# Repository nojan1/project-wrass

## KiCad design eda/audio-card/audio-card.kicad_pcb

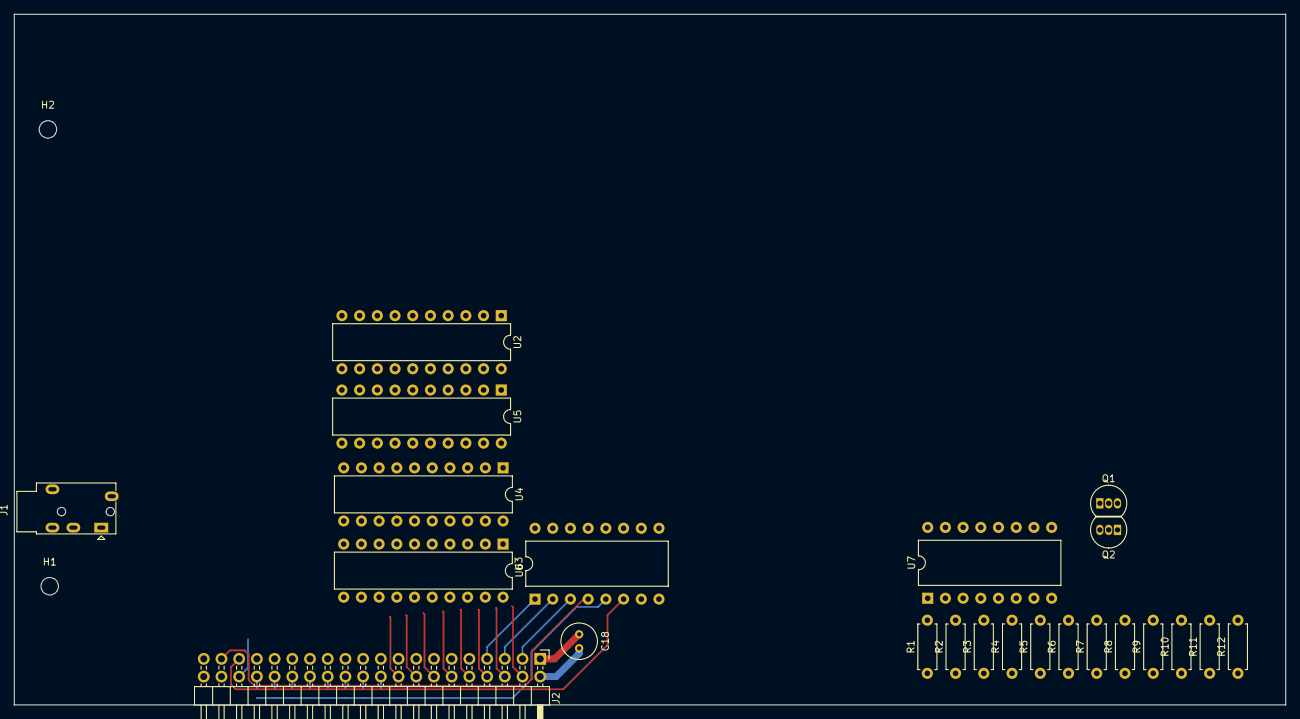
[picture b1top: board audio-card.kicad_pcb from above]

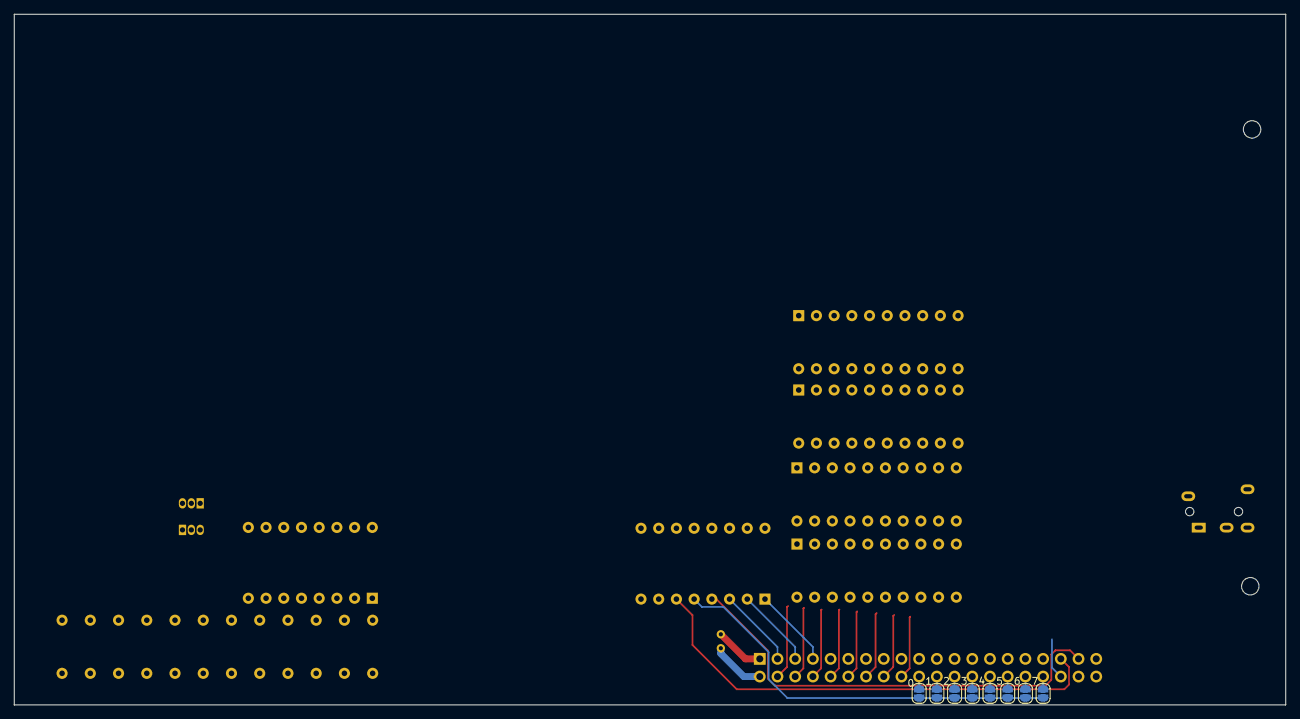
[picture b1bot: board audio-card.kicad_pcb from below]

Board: 2 copper layers, 182.4 x 99.1 mm, 33 parts (8 on the bottom side), 39 nets.

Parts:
C18: 100nf; C_Radial_D5.0mm_H7.0mm_P2.00mm
H1, H2: Bracket mounting; MountingHole_2.5mm
J1: AudioJack2_SwitchT; Jack_3.5mm_PJ320E_Horizontal
J2: Bus expansion; PinHeader_2x20_P2.54mm_Horizontal
JP1, JP2, JP3, JP4, JP5, JP6, JP7, JP8: SolderJumper_2_Open; SolderJumper-2_P1.3mm_Open_RoundedPad1.0x1.5mm
Q1, Q2: BC558; TO-92_Inline
R1, R2, R3: 100k; R_Axial_DIN0207_L6.3mm_D2.5mm_P7.62mm_Horizontal
R4: 100R; R_Axial_DIN0207_L6.3mm_D2.5mm_P7.62mm_Horizontal
R5: 200k; R_Axial_DIN0207_L6.3mm_D2.5mm_P7.62mm_Horizontal
R6: 33k; R_Axial_DIN0207_L6.3mm_D2.5mm_P7.62mm_Horizontal
R7, R8, R9: 10k; R_Axial_DIN0207_L6.3mm_D2.5mm_P7.62mm_Horizontal
R10, R11: 470k; R_Axial_DIN0207_L6.3mm_D2.5mm_P7.62mm_Horizontal
R12: 1k; R_Axial_DIN0207_L6.3mm_D2.5mm_P7.62mm_Horizontal
U2, U4, U5, U6: 74HCT574; DIP-20_W7.62mm
U3: 74HCT138; DIP-16_W10.16mm
U7: TL074; DIP-16_W10.16mm

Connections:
+12V: R1.1, R2.1
/Channel/D0: J2.4, U2.2 (D0), U4.2 (D0), U5.2 (D0), U6.2 (D0)
/Channel/D1: J2.6, U2.3 (D1), U4.3 (D1), U5.3 (D1), U6.3 (D1)
/Channel/D2: J2.8, U2.4 (D2), U4.4 (D2), U5.4 (D2), U6.4 (D2)
/Channel/D3: J2.10, U2.5 (D3), U4.5 (D3), U5.5 (D3), U6.5 (D3)
/Channel/D4: J2.12, U2.6 (D4), U4.6 (D4), U5.6 (D4), U6.6 (D4)
/Channel/D5: J2.14, U2.7 (D5), U4.7 (D5), U5.7 (D5), U6.7 (D5)
/Channel/D6: J2.16, U2.8 (D6), U4.8 (D6), U5.8 (D6), U6.8 (D6)
/Channel/D7: J2.18, U2.9 (D7), U4.9 (D7), U5.9 (D7), U6.9 (D7)
/Channel/~NoteLatch: U2.11 (Cp), U3.14 (O1)
/Channel/~OctaveLatch: U3.15 (O0), U6.11 (Cp)
/Channel/~VolumeLatch: U3.13 (O2), U4.11 (Cp)
/Expansion/A0: J2.3, U3.3 (A2)
/Expansion/A1: J2.5, U3.2 (A1)
/Expansion/A2: J2.7, U3.1 (A0)
/Expansion/Clock: J2.35, U3.6 (E3)
/Expansion/GND: C18.2, J2.2
/Expansion/R~W: J2.37, U3.4 (E1)
/Expansion/VCC: C18.1, J2.1
/Expansion/~CS: JP1.2 (B), JP2.2 (B), JP3.2 (B), JP4.2 (B), JP5.2 (B), JP6.2 (B), JP7.2 (B), JP8.2 (B), U3.5 (E2)
GND: Q2.2 (B), R4.2, R10.2, U2.1 (OE), U2.10 (GND), U4.1 (OE), U4.10 (GND), U5.1 (OE), U5.10 (GND), U6.1 (OE), U6.10 (GND), U7.3 (+)
unnamed: J2.20, JP1.1 (A)
unnamed: J2.22, JP2.1 (A)
unnamed: J2.24, JP3.1 (A)
unnamed: J2.26, JP4.1 (A)
unnamed: J2.28, JP5.1 (A)
unnamed: J2.30, JP6.1 (A)
unnamed: J2.32, JP7.1 (A)
unnamed: J2.34, JP8.1 (A)
unnamed: Q1.2 (B), R3.2, R4.1
unnamed: Q1.1 (C), R1.2, R7.1
unnamed: Q1.3 (E), Q2.3 (E), R9.1
unnamed: Q2.1 (C), R2.2, R8.1
unnamed: R6.2, R9.2, U7.1
unnamed: R11.2, R12.1, U7.7
unnamed: R5.1, R6.1, U7.2 (-)
unnamed: R8.2, R10.1, U7.5 (+)
unnamed: R7.2, R11.1, U7.6 (-)
VCC: U2.20 (VCC), U4.20 (VCC), U5.20 (VCC), U6.20 (VCC)

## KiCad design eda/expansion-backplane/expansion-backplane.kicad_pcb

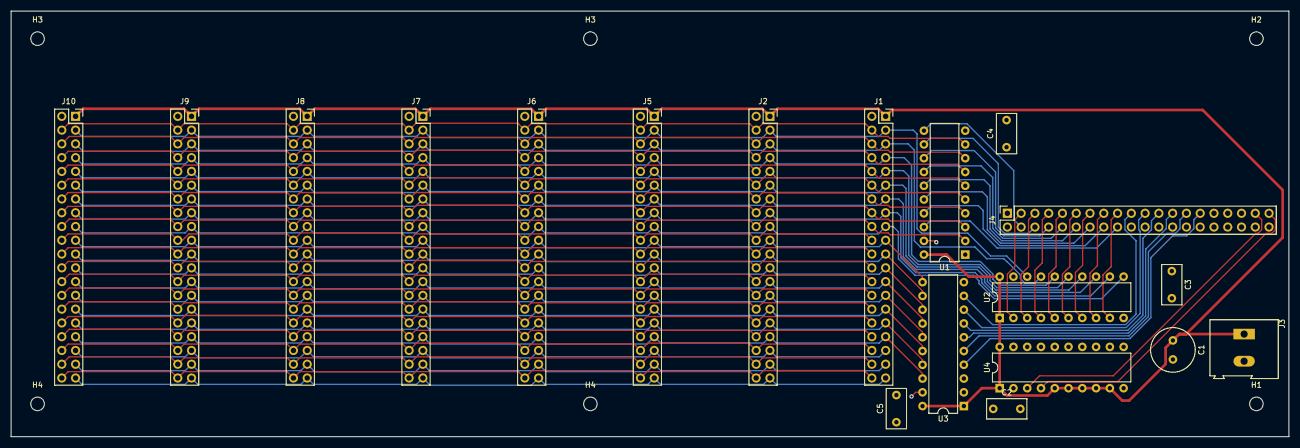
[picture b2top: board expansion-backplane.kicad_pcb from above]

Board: 2 copper layers, 235.7 x 78.5 mm, 25 parts (0 on the bottom side), 67 nets.

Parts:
C1: 1u; C_Radial_D8.0mm_H7.0mm_P3.50mm
C2, C3, C4, C5: 100nf; C_Rect_L7.2mm_W3.5mm_P5.00mm_FKS2_FKP2_MKS2_MKP2
H1, H2, H3, H3#2, H4, H4#2: MountingHole; MountingHole_2.5mm
J1: OUT1; PinSocket_2x20_P2.54mm_Vertical
J2: OUT5; PinSocket_2x20_P2.54mm_Vertical
J3: PWR; TerminalBlock_Altech_AK300-2_P5.00mm
J4: IN; PinSocket_2x20_P2.54mm_Vertical
J5: OUT2; PinSocket_2x20_P2.54mm_Vertical
J6: OUT6; PinSocket_2x20_P2.54mm_Vertical
J7: OUT3; PinSocket_2x20_P2.54mm_Vertical
J8: OUT7; PinSocket_2x20_P2.54mm_Vertical
J9: OUT4; PinSocket_2x20_P2.54mm_Vertical
J10: OUT8; PinSocket_2x20_P2.54mm_Vertical
U1, U2, U3, U4: 74HCT245; DIP-20_W7.62mm

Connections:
/IA0: J4.3, U2.2 (A0)
/IA1: J4.5, U2.3 (A1)
/IA2: J4.7, U2.4 (A2)
/IA3: J4.9, U2.5 (A3)
/IA4: J4.11, U2.6 (A4)
/IA5: J4.13, U2.7 (A5)
/IA6: J4.15, U2.8 (A6)
/IA7: J4.17, U2.9 (A7)
/IA8: J4.19, U3.9 (A7)
/IA9: J4.21, U3.8 (A6)
/IA10: J4.23, U3.7 (A5)
/IA11: J4.25, U3.6 (A4)
/IA12: J4.27, U3.5 (A3)
/IA13: J4.29, U3.4 (A2)
/IA14: J4.31, U3.3 (A1)
/IA15: J4.33, U3.2 (A0)
/IClock: J4.35, U4.2 (A0)
/ID0: J4.4, U1.11 (B7)
/ID1: J4.6, U1.12 (B6)
/ID2: J4.8, U1.13 (B5)
/ID3: J4.10, U1.14 (B4)
/ID4: J4.12, U1.15 (B3)
/ID5: J4.14, U1.16 (B2)
/ID6: J4.16, U1.17 (B1)
/ID7: J4.18, U1.18 (B0)
/IR~W: J4.37, U1.1 (A->B), U4.3 (A1)
/I~DMA: J4.39, U4.4 (A2)
A0: J1.3, J2.3, J5.3, J6.3, J7.3, J8.3, J9.3, J10.3, U2.18 (B0)
A1: J1.5, J2.5, J5.5, J6.5, J7.5, J8.5, J9.5, J10.5, U2.17 (B1)
A2: J1.7, J2.7, J5.7, J6.7, J7.7, J8.7, J9.7, J10.7, U2.16 (B2)
A3: J1.9, J2.9, J5.9, J6.9, J7.9, J8.9, J9.9, J10.9, U2.15 (B3)
A4: J1.11, J2.11, J5.11, J6.11, J7.11, J8.11, J9.11, J10.11, U2.14 (B4)
A5: J1.13, J2.13, J5.13, J6.13, J7.13, J8.13, J9.13, J10.13, U2.13 (B5)
A6: J1.15, J2.15, J5.15, J6.15, J7.15, J8.15, J9.15, J10.15, U2.12 (B6)
A7: J1.17, J2.17, J5.17, J6.17, J7.17, J8.17, J9.17, J10.17, U2.11 (B7)
A8: J1.19, J2.19, J5.19, J6.19, J7.19, J8.19, J9.19, J10.19, U3.11 (B7)
A9: J1.21, J2.21, J5.21, J6.21, J7.21, J8.21, J9.21, J10.21, U3.12 (B6)
A10: J1.23, J2.23, J5.23, J6.23, J7.23, J8.23, J9.23, J10.23, U3.13 (B5)
A11: J1.25, J2.25, J5.25, J6.25, J7.25, J8.25, J9.25, J10.25, U3.14 (B4)
A12: J1.27, J2.27, J5.27, J6.27, J7.27, J8.27, J9.27, J10.27, U3.15 (B3)
A13: J1.29, J2.29, J5.29, J6.29, J7.29, J8.29, J9.29, J10.29, U3.16 (B2)
A14: J1.31, J2.31, J5.31, J6.31, J7.31, J8.31, J9.31, J10.31, U3.17 (B1)
A15: J1.33, J2.33, J5.33, J6.33, J7.33, J8.33, J9.33, J10.33, U3.18 (B0)
Clock: J1.35, J2.35, J5.35, J6.35, J7.35, J8.35, J9.35, J10.35, U4.18 (B0)
D0: J1.4, J2.4, J5.4, J6.4, J7.4, J8.4, J9.4, J10.4, U1.9 (A7)
D1: J1.6, J2.6, J5.6, J6.6, J7.6, J8.6, J9.6, J10.6, U1.8 (A6)
D2: J1.8, J2.8, J5.8, J6.8, J7.8, J8.8, J9.8, J10.8, U1.7 (A5)
D3: J1.10, J2.10, J5.10, J6.10, J7.10, J8.10, J9.10, J10.10, U1.6 (A4)
D4: J1.12, J2.12, J5.12, J6.12, J7.12, J8.12, J9.12, J10.12, U1.5 (A3)
D5: J1.14, J2.14, J5.14, J6.14, J7.14, J8.14, J9.14, J10.14, U1.4 (A2)
D6: J1.16, J2.16, J5.16, J6.16, J7.16, J8.16, J9.16, J10.16, U1.3 (A1)
D7: J1.18, J2.18, J5.18, J6.18, J7.18, J8.18, J9.18, J10.18, U1.2 (A0)
GND: C1.2, C2.2, C3.2, C4.2, C5.2, J1.2, J2.2, J3.2, J4.2, J5.2, J6.2, J7.2, J8.2, J9.2, J10.2, U1.10 (GND), U1.19 (CE), U2.10 (GND), U2.19 (CE), U3.10 (GND), U3.19 (CE), U4.10 (GND), U4.19 (CE)
IO0: J1.20, J2.20, J4.20, J5.20, J6.20, J7.20, J8.20, J9.20, J10.20
IO1: J1.22, J2.22, J4.22, J5.22, J6.22, J7.22, J8.22, J9.22, J10.22
IO2: J1.24, J2.24, J4.24, J5.24, J6.24, J7.24, J8.24, J9.24, J10.24
IO3: J1.26, J2.26, J4.26, J5.26, J6.26, J7.26, J8.26, J9.26, J10.26
IO4: J1.28, J2.28, J4.28, J5.28, J6.28, J7.28, J8.28, J9.28, J10.28
IO5: J1.30, J2.30, J4.30, J5.30, J6.30, J7.30, J8.30, J9.30, J10.30
IO6: J1.32, J2.32, J4.32, J5.32, J6.32, J7.32, J8.32, J9.32, J10.32
IO7: J1.34, J2.34, J4.34, J5.34, J6.34, J7.34, J8.34, J9.34, J10.34
R~W: J1.37, J2.37, J5.37, J6.37, J7.37, J8.37, J9.37, J10.37, U4.17 (B1)
VCC: C1.1, C2.1, C3.1, C4.1, C5.1, J1.1, J2.1, J3.1, J5.1, J6.1, J7.1, J8.1, J9.1, J10.1, U1.20 (VCC), U2.1 (A->B), U2.20 (VCC), U3.1 (A->B), U3.20 (VCC), U4.1 (A->B), U4.5 (A3), U4.6 (A4), U4.7 (A5), U4.8 (A6), U4.9 (A7), U4.20 (VCC)
~DMA: J1.39, J2.39, J5.39, J6.39, J7.39, J8.39, J9.39, J10.39, U4.16 (B2)
~IRQ: J1.40, J2.40, J4.40, J5.40, J6.40, J7.40, J8.40, J9.40, J10.40
~NMI: J1.38, J2.38, J4.38, J5.38, J6.38, J7.38, J8.38, J9.38, J10.38
~RST: J1.36, J2.36, J4.36, J5.36, J6.36, J7.36, J8.36, J9.36, J10.36

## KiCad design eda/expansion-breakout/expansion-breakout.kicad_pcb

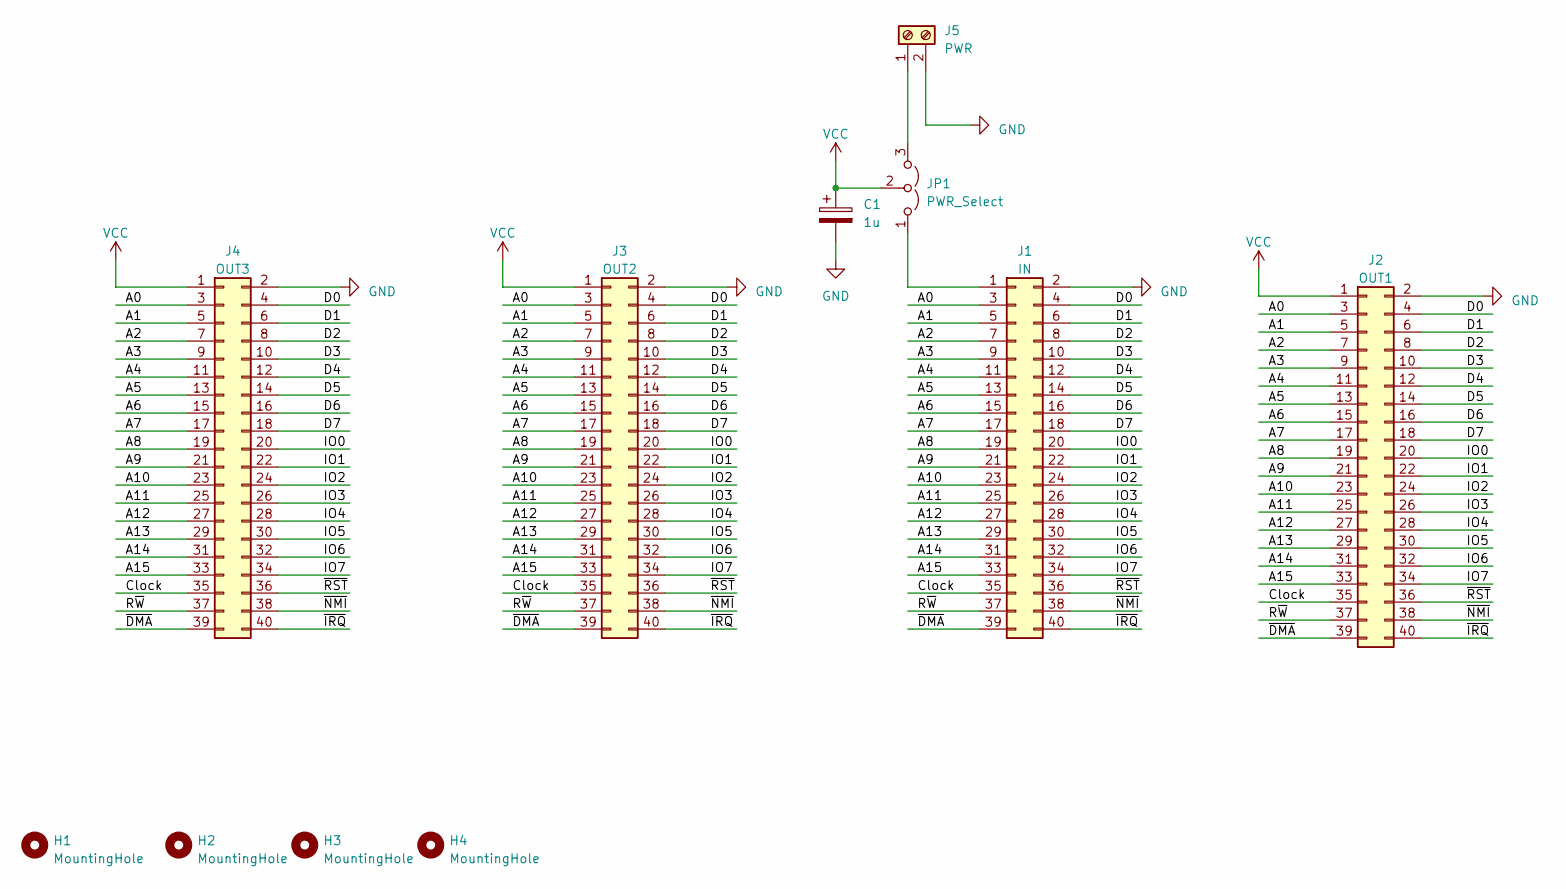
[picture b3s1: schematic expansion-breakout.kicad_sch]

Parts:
C1: 1u; C_Radial_D8.0mm_H7.0mm_P3.50mm
H1, H2, H3, H4: MountingHole; MountingHole_2.5mm
J1: IN; PinHeader_2x20_P2.54mm_Vertical
J2: OUT1; PinHeader_2x20_P2.54mm_Vertical
J3: OUT2; PinSocket_2x20_P2.54mm_Vertical
J4: OUT3; PinSocket_2x20_P2.54mm_Vertical
J5: PWR; TerminalBlock_Altech_AK300-2_P5.00mm
JP1: PWR_Select; PinHeader_1x03_P2.54mm_Vertical

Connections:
/A0: J1.3, J2.3, J3.3, J4.3
/A1: J1.5, J2.5, J3.5, J4.5
/A2: J1.7, J2.7, J3.7, J4.7
/A3: J1.9, J2.9, J3.9, J4.9
/A4: J1.11, J2.11, J3.11, J4.11
/A5: J1.13, J2.13, J3.13, J4.13
/A6: J1.15, J2.15, J3.15, J4.15
/A7: J1.17, J2.17, J3.17, J4.17
/A8: J1.19, J2.19, J3.19, J4.19
/A9: J1.21, J2.21, J3.21, J4.21
/A10: J1.23, J2.23, J3.23, J4.23
/A11: J1.25, J2.25, J3.25, J4.25
/A12: J1.27, J2.27, J3.27, J4.27
/A13: J1.29, J2.29, J3.29, J4.29
/A14: J1.31, J2.31, J3.31, J4.31
/A15: J1.33, J2.33, J3.33, J4.33
/Clock: J1.35, J2.35, J3.35, J4.35
/D0: J1.4, J2.4, J3.4, J4.4
/D1: J1.6, J2.6, J3.6, J4.6
/D2: J1.8, J2.8, J3.8, J4.8
/D3: J1.10, J2.10, J3.10, J4.10
/D4: J1.12, J2.12, J3.12, J4.12
/D5: J1.14, J2.14, J3.14, J4.14
/D6: J1.16, J2.16, J3.16, J4.16
/D7: J1.18, J2.18, J3.18, J4.18
/IO0: J1.20, J2.20, J3.20, J4.20
/IO1: J1.22, J2.22, J3.22, J4.22
/IO2: J1.24, J2.24, J3.24, J4.24
/IO3: J1.26, J2.26, J3.26, J4.26
/IO4: J1.28, J2.28, J3.28, J4.28
/IO5: J1.30, J2.30, J3.30, J4.30
/IO6: J1.32, J2.32, J3.32, J4.32
/IO7: J1.34, J2.34, J3.34, J4.34
/R~W: J1.37, J2.37, J3.37, J4.37
/~DMA: J1.39, J2.39, J3.39, J4.39
/~IRQ: J1.40, J2.40, J3.40, J4.40
/~NMI: J1.38, J2.38, J3.38, J4.38
/~RST: J1.36, J2.36, J3.36, J4.36
GND: C1.2, J1.2, J2.2, J3.2, J4.2, J5.2
unnamed: J1.1, JP1.1 (A)
unnamed: J5.1, JP1.3 (B)
VCC: C1.1, J2.1, J3.1, J4.1, JP1.2 (C)

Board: 2 copper layers, 11 parts (2 on the bottom side), 42 nets, no tracks yet.

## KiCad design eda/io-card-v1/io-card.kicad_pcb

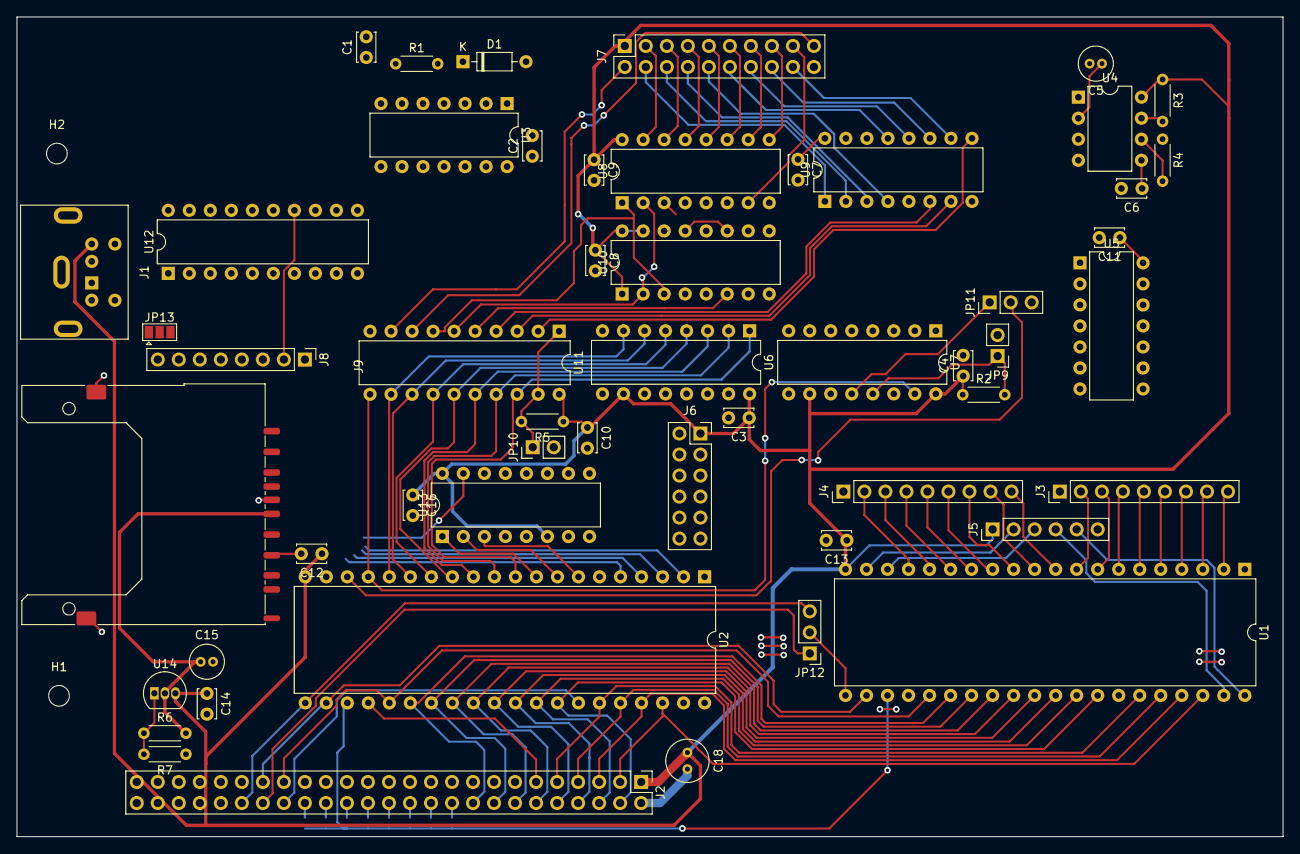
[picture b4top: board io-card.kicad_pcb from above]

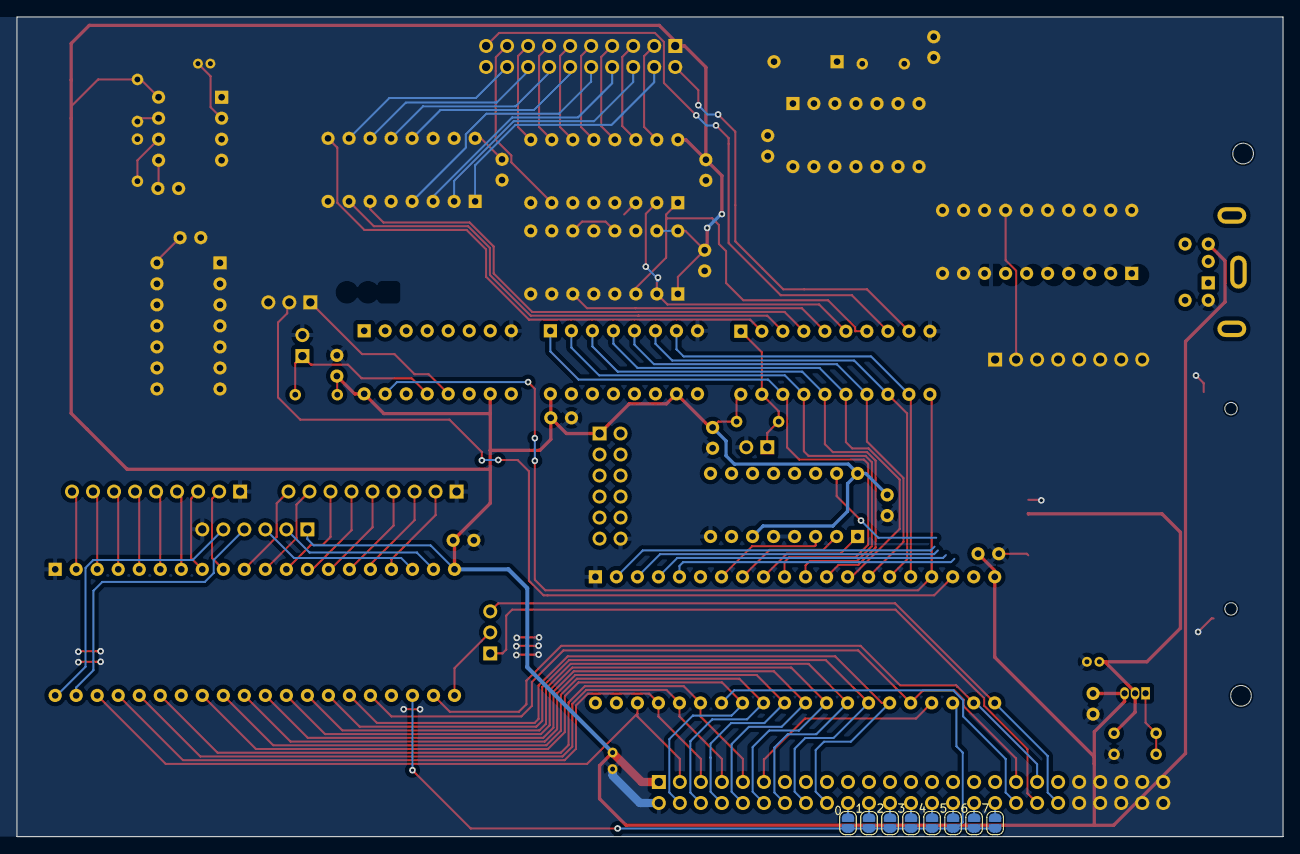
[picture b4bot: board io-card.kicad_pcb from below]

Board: 2 copper layers, 153.0 x 99.1 mm, 63 parts (8 on the bottom side), 124 nets.

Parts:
C1, C2, C3, C4, C6, C7, C8, C9, C10, C11, C12, C13, C14, C16: 100nf; C_Disc_D3.4mm_W2.1mm_P2.50mm
C5: 220nf; C_Radial_D4.0mm_H5.0mm_P1.50mm
C15: 100nf; C_Radial_D4.0mm_H5.0mm_P1.50mm
C18: 100nf; C_Radial_D5.0mm_H7.0mm_P2.00mm
D1: 1N457; D_DO-35_SOD27_P7.62mm_Horizontal
H1, H2: MountingHole; MountingHole_2.5mm
J1: PS2; Connector_Mini-DIN_Female_6Pin_2rows
J2: Conn_02x25_Odd_Even; PinHeader_2x25_P2.54mm_Vertical
J3: PortA; PinHeader_1x09_P2.54mm_Vertical
J4: PortB; PinHeader_1x09_P2.54mm_Vertical
J5: ControlLines; PinHeader_1x06_P2.54mm_Vertical
J6: SPI; PinSocket_2x06_P2.54mm_Vertical
J7: Keyboard connector; PinSocket_2x10_P2.54mm_Vertical
J8: SD-Card module; PinHeader_1x08_P2.54mm_Vertical
J9: SD_Card; SD_Kyocera_145638109511859+
JP1, JP2, JP3, JP4, JP5, JP6, JP7, JP8: SolderJumper_2_Open; SolderJumper-2_P1.3mm_Open_RoundedPad1.0x1.5mm
JP9: Enable PS2 Output; PinHeader_1x02_P2.54mm_Vertical
JP10: Enable Scanning Keyboard Output; PinHeader_1x02_P2.54mm_Vertical
JP11: Key present select; PinHeader_1x03_P2.54mm_Vertical
JP12: IRQ Select; PinHeader_1x03_P2.54mm_Vertical
JP13: SD-Card voltage select; SolderJumper-3_P1.3mm_Open_Pad1.0x1.5mm
R1: 33k; R_Axial_DIN0204_L3.6mm_D1.6mm_P5.08mm_Horizontal
R2, R5: 10k; R_Axial_DIN0204_L3.6mm_D1.6mm_P5.08mm_Horizontal
R3: 1.5k; R_Axial_DIN0204_L3.6mm_D1.6mm_P5.08mm_Horizontal
R4: 22k; R_Axial_DIN0204_L3.6mm_D1.6mm_P5.08mm_Horizontal
R6: 220R; R_Axial_DIN0204_L3.6mm_D1.6mm_P5.08mm_Horizontal
R7: 370R; R_Axial_DIN0204_L3.6mm_D1.6mm_P5.08mm_Horizontal
U1, U2: W65C22SxP; DIP-40_W15.24mm
U3: 74HCT14; DIP-14_W7.62mm
U4: NE555P; DIP-8_W7.62mm
U5: 74HCT00; DIP-14_W7.62mm
U6, U7: 74HCT595; DIP-16_W7.62mm
U8, U13: 74HCT138; DIP-16_W7.62mm
U9: 74HCT148; DIP-16_W7.62mm
U10: 74HCT193; DIP-16_W7.62mm
U11: 74HCT541; DIP-20_W7.62mm
U12: 74HC541; DIP-20_W7.62mm
U14: LM317L_TO92; TO-92_Inline

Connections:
+3.3V: C15.1, J9.4 (VDD), JP13.3 (B), R6.2, U12.20 (VCC), U14.2 (VO)
/Clock: J2.39, U1.25 (ϕ2), U2.25 (ϕ2)
/Expansion header/A0: J2.5, U1.38 (RS0), U2.38 (RS0)
/Expansion header/A1: J2.7, U1.37 (RS1), U2.37 (RS1)
/Expansion header/A2: J2.9, U1.36 (RS2), U2.36 (RS2)
/Expansion header/A3: J2.11, U1.35 (RS3), U2.35 (RS3)
/Expansion header/A4: J2.13, U2.24 (CS1), U3.9
/Expansion header/D0: J2.4, U1.33 (D0), U2.33 (D0)
/Expansion header/D1: J2.6, U1.32 (D1), U2.32 (D1)
/Expansion header/D2: J2.8, U1.31 (D2), U2.31 (D2)
/Expansion header/D3: J2.10, U1.30 (D3), U2.30 (D3)
/Expansion header/D4: J2.12, U1.29 (D4), U2.29 (D4)
/Expansion header/D5: J2.14, U1.28 (D5), U2.28 (D5)
/Expansion header/D6: J2.16, U1.27 (D6), U2.27 (D6)
/Expansion header/D7: J2.18, U1.26 (D7), U2.26 (D7)
/PS2 keyboard interface/KeyPresent: JP11.1 (A), U3.6, U6.12 (RCLK), U7.12 (RCLK)
/PS2 keyboard interface/KeyboardBit0: U2.10 (PB0), U6.1 (QB), U11.18 (Y0)
/PS2 keyboard interface/KeyboardBit1: U2.11 (PB1), U6.2 (QC), U11.17 (Y1)
/PS2 keyboard interface/KeyboardBit2: U2.12 (PB2), U6.3 (QD), U11.16 (Y2)
/PS2 keyboard interface/KeyboardBit3: U2.13 (PB3), U6.4 (QE), U11.15 (Y3)
/PS2 keyboard interface/KeyboardBit4: U2.14 (PB4), U6.5 (QF), U11.14 (Y4)
/PS2 keyboard interface/KeyboardBit5: U2.15 (PB5), U6.6 (QG), U11.13 (Y5)
/PS2 keyboard interface/KeyboardBit6: U2.16 (PB6), U6.7 (QH), U11.12 (Y6)
/PS2 keyboard interface/KeyboardBit7: U2.17 (PB7), U7.15 (QA), U11.11 (Y7)
/PS2 keyboard interface/KeyboardData: J1.1, U6.14 (SER)
/PS2 keyboard interface/~KeyboardClk: U3.4, U6.11 (SRCLK), U7.11 (SRCLK)
/PS2 keyboard interface/~PS2ShiftOE: JP9.1 (A), R2.2, U6.13 (~OE), U7.13 (~OE)
/R~W: J2.41, U1.22 (R/~W), U2.22 (R/~W)
/SD-Card/SD_CLK: J8.4, J9.5 (CLK), U12.16 (Y2)
/SD-Card/SD_CS: J8.3, J9.1 (CD/DAT3), U12.18 (Y0)
/SD-Card/SD_CardDetect: J8.2, J9.10 (CARD_DETECT), U12.14 (Y4)
/SD-Card/SD_SDI: J8.5, J9.7 (DAT0), U12.5 (A3)
/SD-Card/SD_SDO: J8.6, J9.2 (CMD), U12.17 (Y1)
/SD-Card/SD_WriteProtect: J8.7, J9.11 (WRITE_PROTECT), U12.13 (Y5)
/SD-Card/WriteProtect: U2.6 (PA4), U12.7 (A5)
/SD-Card/~CS: U12.2 (A0), U13.15 (O0)
/SPI_CLK: J6.7, U2.4 (PA2), U12.4 (A2)
/SPI_MISO: J6.5, U2.3 (PA1), U12.15 (Y3)
/SPI_MOSI: J6.3, U2.2 (PA0), U12.3 (A1)
/Scanning keyboard interface/KeyPresent: JP11.3 (B), U5.3
/Scanning keyboard interface/KeyboardScanClock: U4.3 (Q), U5.2, U10.4 (DOWN)
/Scanning keyboard interface/Scancode0: U8.1 (A0), U10.3 (QA), U11.7 (A5)
/Scanning keyboard interface/Scancode1: U8.2 (A1), U10.2 (QB), U11.6 (A4)
/Scanning keyboard interface/Scancode2: U8.3 (A2), U10.6 (QC), U11.5 (A3)
/Scanning keyboard interface/Scancode3: U9.9 (S0), U11.2 (A0)
/Scanning keyboard interface/Scancode4: U9.7 (S1), U11.3 (A1)
/Scanning keyboard interface/Scancode5: U9.6 (S2), U11.4 (A2)
/Scanning keyboard interface/col0: J7.3, U8.15 (O0)
/Scanning keyboard interface/col1: J7.5, U8.14 (O1)
/Scanning keyboard interface/col2: J7.7, U8.13 (O2)
/Scanning keyboard interface/col3: J7.9, U8.12 (O3)
/Scanning keyboard interface/col4: J7.11, U8.11 (O4)
/Scanning keyboard interface/col5: J7.13, U8.10 (O5)
/Scanning keyboard interface/col6: J7.15, U8.9 (O6)
/Scanning keyboard interface/col7: J7.17, U8.7 (O7)
/Scanning keyboard interface/mod0: J7.2, U11.9 (A7)
/Scanning keyboard interface/mod1: J7.19, U11.8 (A6)
/Scanning keyboard interface/row0: J7.18, U9.10 (IO)
/Scanning keyboard interface/row1: J7.16, U9.11 (I1)
/Scanning keyboard interface/row2: J7.14, U9.12 (I2)
/Scanning keyboard interface/row3: J7.12, U9.13 (I3)
/Scanning keyboard interface/row4: J7.10, U9.4 (I7)
/Scanning keyboard interface/row5: J7.8, U9.3 (I6)
/Scanning keyboard interface/row6: J7.6, U9.2 (I5)
/Scanning keyboard interface/row7: J7.4, U9.1 (I4)
/~CS: JP1.2 (B), JP2.2 (B), JP3.2 (B), JP4.2 (B), JP5.2 (B), JP6.2 (B), JP7.2 (B), JP8.2 (B), U1.23 (~CS2), U2.23 (~CS2)
/~IRQ: J2.44, JP12.3 (B), U2.21 (~IRQ)
/~NMI: J2.42, JP12.1 (A)
/~RST: J2.40, U1.34 (~RES), U2.34 (~RES)
/~SPI_CS1: J6.9, U13.14 (O1)
/~SPI_CS2: J6.11, U13.13 (O2)
/~SPI_CS3: J6.2, U13.12 (O3)
/~SPI_CS4: J6.4, U13.11 (O4)
/~SPI_CS5: J6.6, U13.10 (O5)
/~SPI_CS6: J6.8, U13.9 (O6)
/~SPI_CS7: J6.10, U13.7 (O7)
GND: C1.2, C2.2, C3.2, C4.2, C5.2, C6.2, C7.2, C8.2, C9.2, C10.2, C11.2, C12.2, C13.2, C14.2, C15.2, C16.2, C18.2, J1.3, J2.2, J2.3, J2.20, J2.37, J2.38, J2.45, J2.46, J3.1, J4.1, J5.6, J6.12, J7.20, J8.1, J9.3 (VSS), J9.6 (VSS), J9.12 (SHELL1), J9.13 (SHELL2), JP9.2 (B), JP10.2 (B), R7.1, U1.1 (VSS), U2.1 (VSS), U3.7 (GND), U4.1 (GND), U5.7 (GND), U6.8 (GND), U7.8 (GND), U8.4 (E1), U8.5 (E2), U8.8 (GND), U9.5 (EI), U9.8 (GND), U10.8 (GND), U10.10 (C), U10.14 (CLR), U11.10 (GND), U12.1 (G1), U12.8 (A6), U12.9 (A7), U12.10 (GND), U12.19 (G2), U13.4 (E1), U13.5 (E2), U13.8 (GND)
unnamed: D1.2 (A), R1.2, U3.2
unnamed: C1.1, D1.1 (K), R1.1, U3.5
unnamed: J1.5, U3.1, U3.3
unnamed: J2.22, JP1.1 (A)
unnamed: J2.24, JP2.1 (A)
unnamed: J2.26, JP3.1 (A)
unnamed: J2.28, JP4.1 (A)
unnamed: J2.30, JP5.1 (A)
unnamed: J2.32, JP6.1 (A)
unnamed: J2.34, JP7.1 (A)
unnamed: J2.36, JP8.1 (A)
unnamed: J3.2, U1.9 (PA7)
unnamed: J3.3, U1.8 (PA6)
unnamed: J3.4, U1.7 (PA5)
unnamed: J3.5, U1.6 (PA4)
unnamed: J3.6, U1.5 (PA3)
unnamed: J3.7, U1.4 (PA2)
unnamed: J3.8, U1.3 (PA1)
unnamed: J3.9, U1.2 (PA0)
unnamed: J4.2, U1.17 (PB7)
unnamed: J4.3, U1.16 (PB6)
unnamed: J4.4, U1.15 (PB5)
unnamed: J4.5, U1.14 (PB4)
unnamed: J4.6, U1.13 (PB3)
unnamed: J4.7, U1.12 (PB2)
unnamed: J4.8, U1.11 (PB1)
unnamed: J4.9, U1.10 (PB0)
unnamed: J5.2, U1.19 (CB2)
unnamed: J5.3, U1.18 (CB1)
unnamed: J5.4, U1.39 (CA2)
unnamed: J5.5, U1.40 (CA1)
unnamed: J8.8, JP13.2 (C)
unnamed: JP10.1 (A), R5.2, U11.1 (G1), U11.19 (G2)
unnamed: JP11.2 (C), U2.18 (CB1)
unnamed: JP12.2 (C), U1.21 (~IRQ)
unnamed: U1.24 (CS1), U3.8
unnamed: C6.1, U4.5 (CV)
unnamed: R3.2, R4.1, U4.7 (DIS)
unnamed: C5.1, R4.2, U4.2 (TR), U4.6 (THR)
unnamed: U6.9 (QH'), U7.14 (SER)
unnamed: U5.1, U9.14 (GS)
unnamed: U10.11 (~LOAD), U10.13 (~BO)
unnamed: U2.9 (PA7), U13.1 (A0)
unnamed: U2.8 (PA6), U13.2 (A1)
unnamed: U2.7 (PA5), U13.3 (A2)
unnamed: R6.1, R7.2, U14.1 (ADJ)
VCC: C2.1, C3.1, C4.1, C7.1, C8.1, C9.1, C10.1, C11.1, C12.1, C13.1, C14.1, C16.1, C18.1, J1.4, J2.1, J5.1, J6.1, J7.1, JP13.1 (A), R2.1, R3.1, R5.1, U1.20 (VCC), U2.20 (VCC), U3.14 (VCC), U4.4 (R), U4.8 (VCC), U5.14 (VCC), U6.10 (~SRCLR), U6.16 (VCC), U7.10 (~SRCLR), U7.16 (VCC), U8.6 (E3), U8.16 (VCC), U9.16 (VCC), U10.1 (B), U10.9 (D), U10.15 (A), U10.16 (VCC), U11.20 (VCC), U13.6 (E3), U13.16 (VCC), U14.3 (VI)
